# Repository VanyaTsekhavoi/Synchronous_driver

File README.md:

# Synchronous_driver
TODO:
* Add diode leading to 3v3 to the output of the current sensor + opamp.
* Add input filter (optional)

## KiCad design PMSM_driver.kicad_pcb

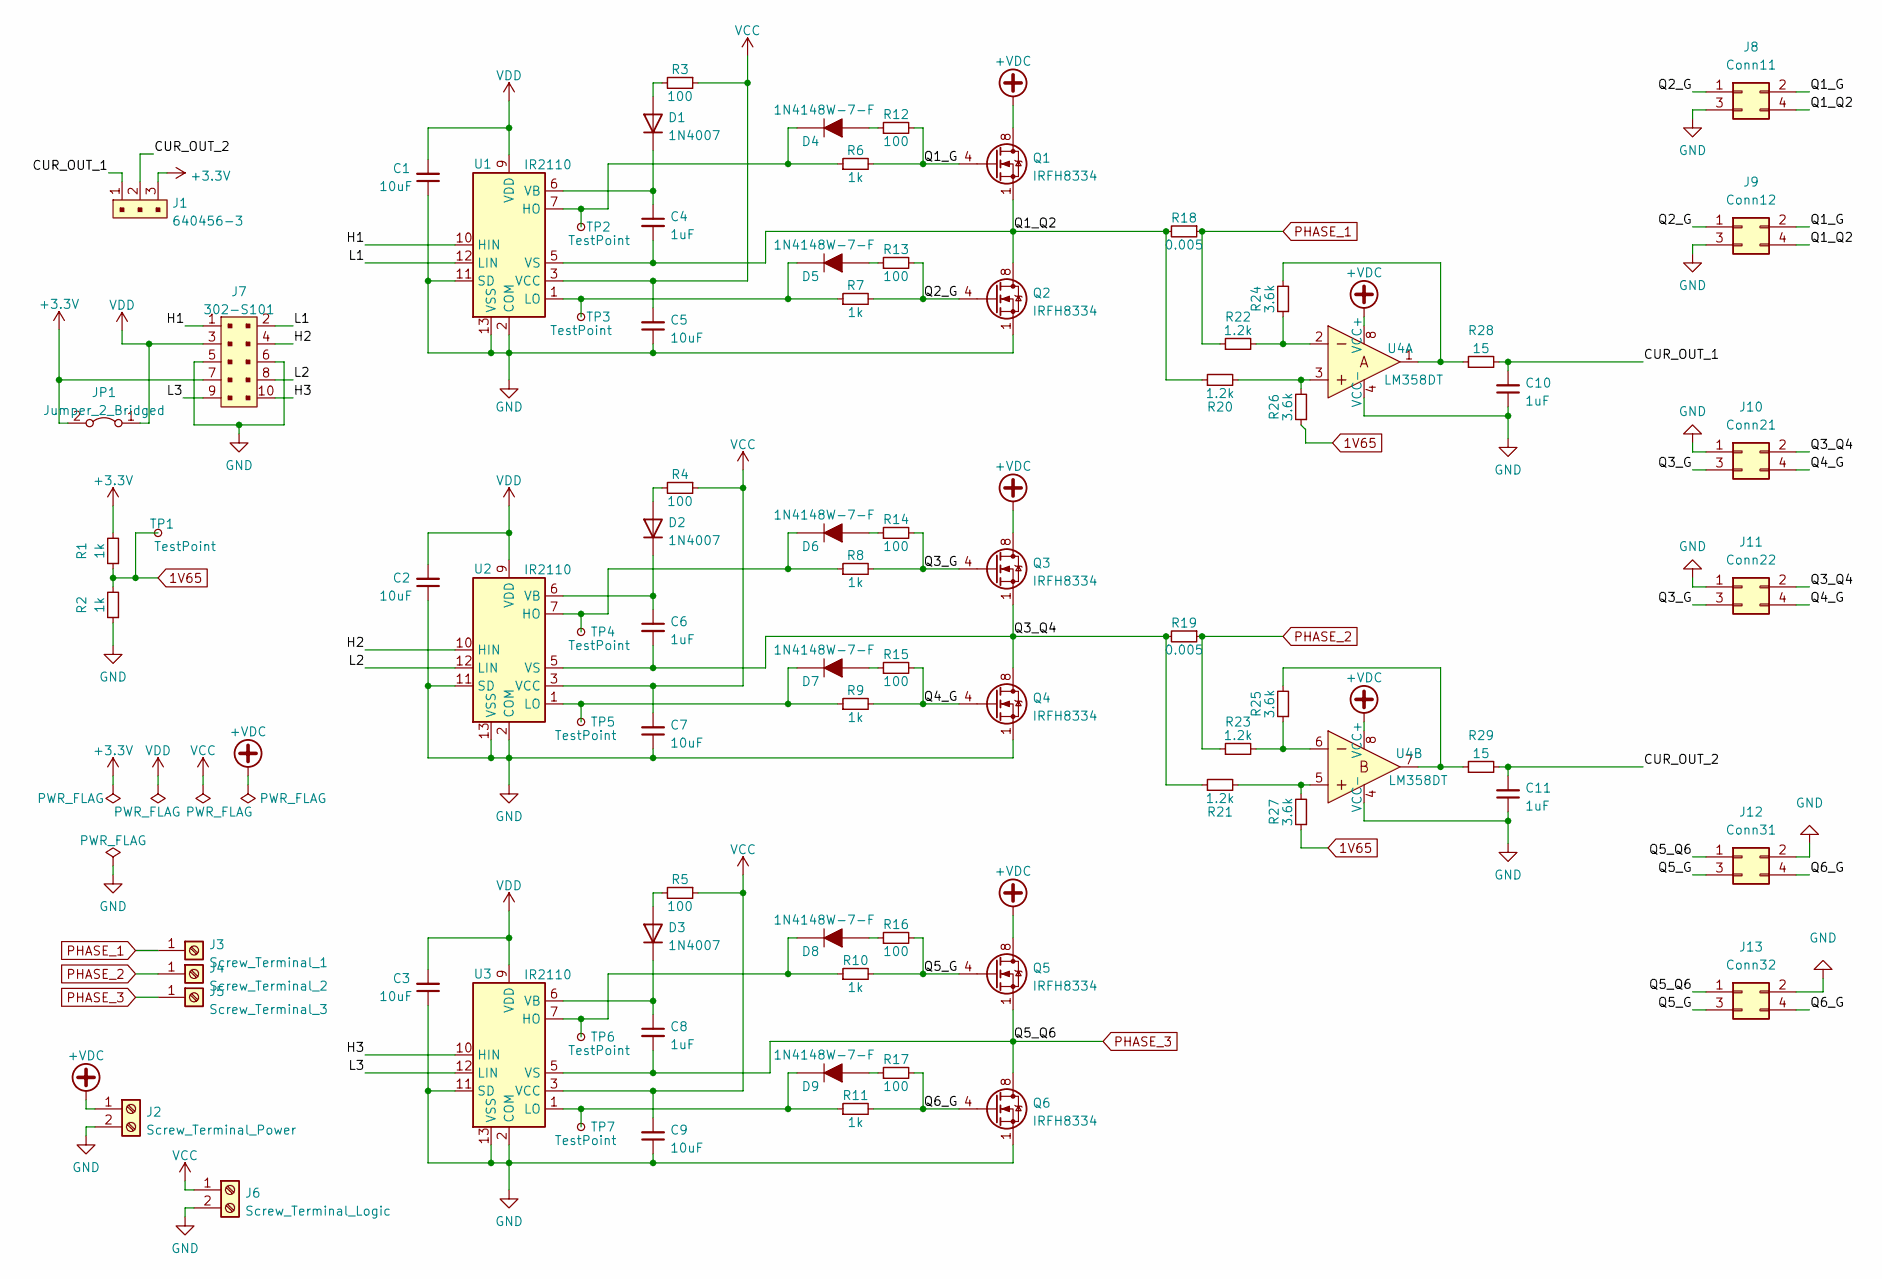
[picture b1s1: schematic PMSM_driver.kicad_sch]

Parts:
C1, C2, C3, C5, C7, C9: 10uF; C_1210_3225Metric_Pad1.33x2.70mm_HandSolder
C4, C6, C8, C10, C11: 1uF; C_0805_2012Metric_Pad1.18x1.45mm_HandSolder
D1, D2, D3: 1N4007; D_DO-41_SOD81_P10.16mm_Horizontal
D4, D5, D6, D7, D8, D9: 1N4148W-7-F; SOD-123; MPN 1N4148W-7-F; Digi-Key_PN 1N4148W-FDICT-ND
J1: 640456-3; PinHeader_1x03_P2.54mm_Vertical; MPN 640456-3; Digi-Key_PN A19470-ND
J2: Screw_Terminal_Power; TerminalBlock_Phoenix_MKDS-1,5-2_1x02_P5.00mm_Horizontal
J3: Screw_Terminal_1; TestPoint_Pad_4.0x4.0mm
J4: Screw_Terminal_2; TestPoint_Pad_4.0x4.0mm
J5: Screw_Terminal_3; TestPoint_Pad_4.0x4.0mm
J6: Screw_Terminal_Logic; TerminalBlock_Phoenix_MKDS-1,5-2_1x02_P5.00mm_Horizontal
J7: 302-S101; PinHeader_2x05_P2.54mm_Vertical; MPN 302-S101; Digi-Key_PN ED1543-ND
J8: Conn11; PinHeader_2x02_P2.54mm_Vertical
J9: Conn12; PinHeader_2x02_P2.54mm_Vertical
J10: Conn21; PinHeader_2x02_P2.54mm_Vertical
J11: Conn22; PinHeader_2x02_P2.54mm_Vertical
J12: Conn31; PinHeader_2x02_P2.54mm_Vertical
J13: Conn32; PinHeader_2x02_P2.54mm_Vertical
JP1: Jumper_2_Bridged; SolderJumper-2_P1.3mm_Open_RoundedPad1.0x1.5mm
Q1, Q2, Q3, Q4, Q5, Q6: IRFH8334; IFX-PQFN-5X6E-V
R1, R2, R6, R7, R8, R9, R10, R11: 1k; R_0603_1608Metric_Pad0.98x0.95mm_HandSolder
R3, R4, R5, R12, R13, R14, R15, R16, R17: 100; R_0603_1608Metric_Pad0.98x0.95mm_HandSolder
R18, R19: 0.005; R_2512_6332Metric_Pad1.40x3.35mm_HandSolder
R20, R21, R22, R23: 1.2k; R_0603_1608Metric_Pad0.98x0.95mm_HandSolder
R24, R25, R26, R27: 3.6k; R_0603_1608Metric_Pad0.98x0.95mm_HandSolder
R28, R29: 15; R_0603_1608Metric_Pad0.98x0.95mm_HandSolder
TP1, TP2, TP3, TP4, TP5, TP6, TP7: TestPoint; TestPoint_Pad_D1.5mm
U1, U2, U3: IR2110; DIP-14_W7.62mm
U4: LM358DT; SOIC-8_W3.9mm; MPN LM358DT; Digi-Key_PN 497-1591-1-ND

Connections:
1V65: R1.1, R2.2, R26.1, R27.1, TP1.1
+3.3V: J1.3, J7.7, JP1.2 (B), R1.2
+VDC: J2.1, Q1.5 (D), Q1.6 (D), Q1.7 (D), Q1.8 (D), Q3.5 (D), Q3.6 (D), Q3.7 (D), Q3.8 (D), Q5.5 (D), Q5.6 (D), Q5.7 (D), Q5.8 (D), U4.8 (VCC+)
/CUR_OUT_1: C10.2, J1.1, R28.2
/CUR_OUT_2: C11.2, J1.2, R29.2
/H1: J7.1, U1.10 (HIN)
/H2: J7.4, U2.10 (HIN)
/H3: J7.10, U3.10 (HIN)
/L1: J7.2, U1.12 (LIN)
/L2: J7.8, U2.12 (LIN)
/L3: J7.9, U3.12 (LIN)
/Q1_G: J8.2, J9.2, Q1.4 (G), R6.2, R12.2
/Q1_Q2: C4.2, J8.4, J9.4, Q1.1 (S), Q1.2 (S), Q1.3 (S), Q2.5 (D), Q2.6 (D), Q2.7 (D), Q2.8 (D), R18.2, R20.1, U1.5 (VS)
/Q2_G: J8.1, J9.1, Q2.4 (G), R7.2, R13.2
/Q3_G: J10.3, J11.3, Q3.4 (G), R8.2, R14.2
/Q3_Q4: C6.2, J10.2, J11.2, Q3.1 (S), Q3.2 (S), Q3.3 (S), Q4.5 (D), Q4.6 (D), Q4.7 (D), Q4.8 (D), R19.2, R21.1, U2.5 (VS)
/Q4_G: J10.4, J11.4, Q4.4 (G), R9.2, R15.2
/Q5_G: J12.3, J13.3, Q5.4 (G), R10.2, R16.2
/Q6_G: J12.4, J13.4, Q6.4 (G), R11.2, R17.2
GND: C1.1, C2.1, C3.1, C5.1, C7.1, C9.1, C10.1, C11.1, J2.2, J6.2, J7.5, J7.6, J8.3, J9.3, J10.1, J11.1, J12.2, J13.2, Q2.1 (S), Q2.2 (S), Q2.3 (S), Q4.1 (S), Q4.2 (S), Q4.3 (S), Q6.1 (S), Q6.2 (S), Q6.3 (S), R2.1, U1.2 (COM), U1.11 (SD), U1.13 (VSS), U2.2 (COM), U2.11 (SD), U2.13 (VSS), U3.2 (COM), U3.11 (SD), U3.13 (VSS), U4.4 (VCC-)
unnamed: C4.1, D1.1 (K), U1.6 (VB)
unnamed: C6.1, D2.1 (K), U2.6 (VB)
unnamed: C8.1, D3.1 (K), U3.6 (VB)
unnamed: D1.2 (A), R3.2
unnamed: D2.2 (A), R4.2
unnamed: D3.2 (A), R5.2
unnamed: D4.A, R12.1
unnamed: D4.K, R6.1, TP2.1, U1.7 (HO)
unnamed: D5.A, R13.1
unnamed: D5.K, R7.1, TP3.1, U1.1 (LO)
unnamed: D6.A, R14.1
unnamed: D6.K, R8.1, TP4.1, U2.7 (HO)
unnamed: D7.A, R15.1
unnamed: D7.K, R9.1, TP5.1, U2.1 (LO)
unnamed: D8.A, R16.1
unnamed: D8.K, R10.1, TP6.1, U3.7 (HO)
unnamed: D9.A, R17.1
unnamed: D9.K, R11.1, TP7.1, U3.1 (LO)
unnamed: R20.2, R26.2, U4.3
unnamed: R21.2, R27.2, U4.5
unnamed: R22.2, R24.1, U4.2
unnamed: R23.2, R25.1, U4.6
unnamed: R24.2, R28.1, U4.1
unnamed: R25.2, R29.1, U4.7
PHASE_1: J3.1, R18.1, R22.1
PHASE_2: J4.1, R19.1, R23.1
PHASE_3: C8.2, J5.1, J12.1, J13.1, Q5.1 (S), Q5.2 (S), Q5.3 (S), Q6.5 (D), Q6.6 (D), Q6.7 (D), Q6.8 (D), U3.5 (VS)
VCC: C5.2, C7.2, C9.2, J6.1, R3.1, R4.1, R5.1, U1.3 (VCC), U2.3 (VCC), U3.3 (VCC)
VDD: C1.2, C2.2, C3.2, J7.3, JP1.1 (A), U1.9 (VDD), U2.9 (VDD), U3.9 (VDD)

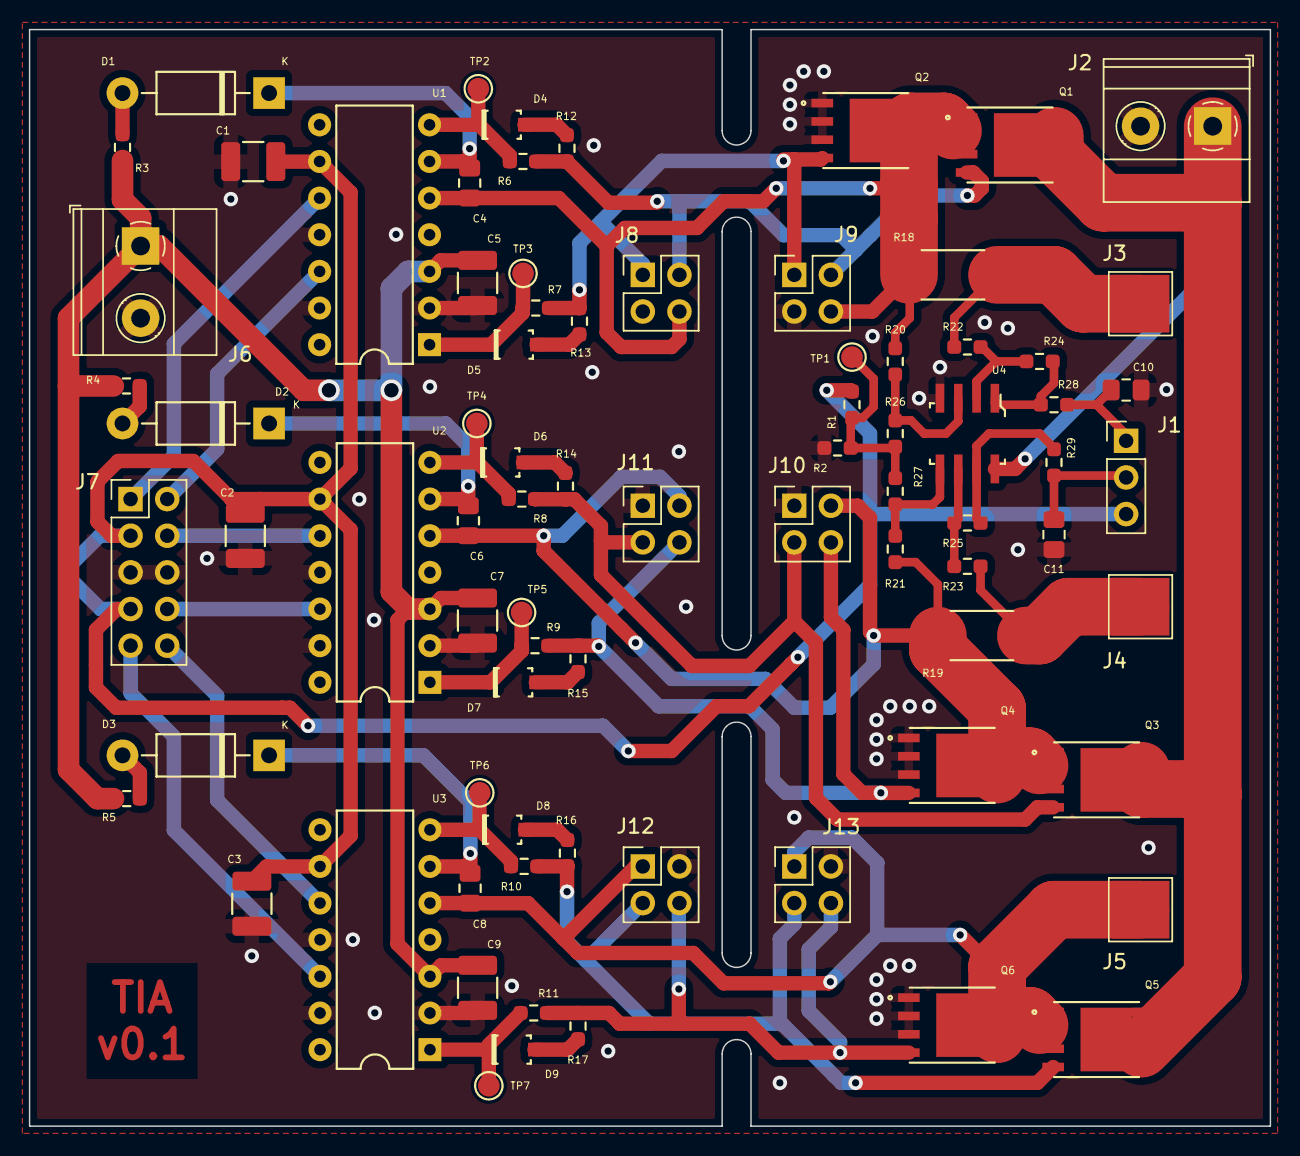
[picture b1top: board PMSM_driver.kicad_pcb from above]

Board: 2 copper layers, 86.0 x 76.0 mm, 80 parts (1 on the bottom side), 49 nets.

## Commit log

2022-12-21 [scheme]: Synchronous driver
2022-12-24 [sheme]: end of schematic + footprints assigment + bom
2023-01-03 [PCB]: PCB design started. Schematic updated.
2023-01-05 [PCB]: components arrangment around 3 MOSFET drivers
2023-01-06 [PCB]: added Power part of the board. Logic part rearrangement
2023-01-06 [PCB]: update panelization libs
2023-01-07 [PCB]: Mosfets rearrangement
2023-01-07 [Repo]: Libs path issue was fixed
2023-01-11 [PCB]: size optimization
2023-01-12 [PCB]: One side placement
2023-01-13 [PCB]: added output connectors for another MOSFETs board
2023-01-14 [PCB]: Power board layout completion
2023-01-15 [PCB]: Logic - Power boards tracing
2023-01-16 [DRC]: DRC checks were passed
2023-01-19 [PCB]: JLCPCB constraints
2023-01-20 [PCB]: Power traces enlargement
2023-01-20 [gerber]: gerber files generation

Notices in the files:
PMSM_driver.kicad_pcb:
creativecommons.org/licences/by/4.0
License: CC BY 4.0
PMSM_driver.kicad_sch:
Licanse: CC BY 4.0
